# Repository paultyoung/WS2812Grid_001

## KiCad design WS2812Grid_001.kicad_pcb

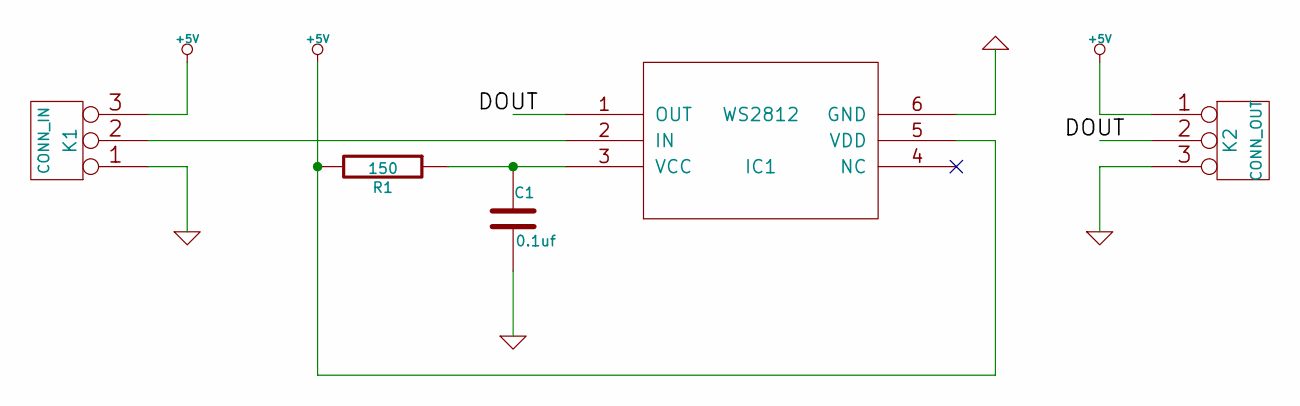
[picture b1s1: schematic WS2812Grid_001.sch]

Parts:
C1: 0.1uf
IC1: WS2812; MODULE
K1: CONN_IN
K2: CONN_OUT
R1: 150

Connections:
+5V: IC1.5 (VDD), K1.3, K2.1, R1.2
/DOUT: IC1.1 (OUT), K2.2 (PM)
GND: C1.2, IC1.6 (GND), K1.1, K2.3
unnamed: IC1.2 (IN), K1.2 (PM)
unnamed: C1.1, IC1.3 (VCC), R1.1

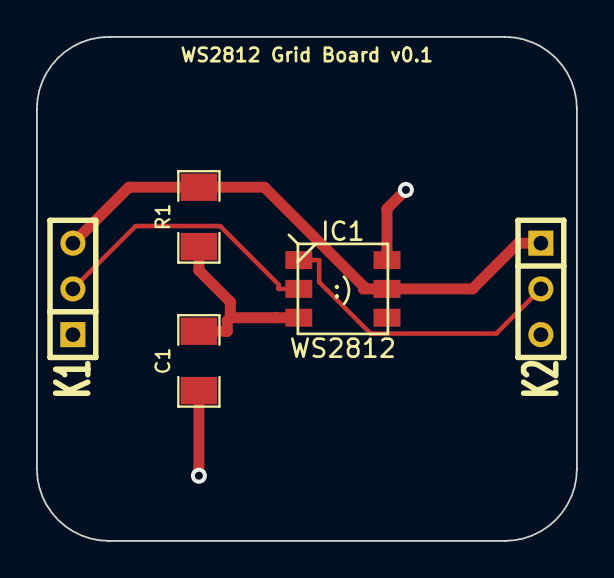
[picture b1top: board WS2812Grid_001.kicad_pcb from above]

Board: 2 copper layers, 30.0 x 28.0 mm, 5 parts (0 on the bottom side), 5 nets.

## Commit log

2014-02-24 Initial Commit
    Committing files to Git for the first time. The project is already
    finished.
